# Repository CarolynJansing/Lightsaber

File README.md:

# Lightsaber
A lightsaber is a fictional energy sword featured in the Star Wars franchise. This project is a simulation of a lightsaber using LEDs, Sound and an Arduino microcontroller. It is based on the Gyversaber. https://www.instructables.com/Arduino-Based-Lightsaber-With-Light-and-Sound-Effe/

## Files

ArduinoCode : GyverSaber/GyverSaber/Gyversaber.ino

SD Files : GyverSaber/SDsounds

Schemes: PCB/

## Getting Started
These instructions will help you get a copy of the project up and running on your local machine for development and testing purposes.

### Prerequisites
To use this project, you will need the following:

Arduino IDE (https://www.arduino.cc/software)
•	Arduino NANO 
•	Adressable LED stripes WS2811, 12V
•	Button with LED 
•	MPU6050 
•	DF-Player
•	Batteries 18650 with Protection
•	DCDC Step-Down
•	Speaker
•	Resistors
•	Power button
•	Charging port
•	CC CV Charger for 3 cells
•	PCB-Board
•	Blade Pipe
•	PVC Pipes for hilt
•	Wire
•	3D druck
•	Soldering Supplies
I chose to use an PCB aswell you can configure it with my files on JLCPCB

### Installing
Clone the repository to your local machine: git clone https://github.com/CarolynJansing/Lightsaber.git
Open the Arduino IDE and open the Gyversaber.ino file from the cloned repository.
Connect the Arduino microcontroller to your computer using a USB cable.
Select the correct board and port in the Arduino IDE (Tools > Board and Tools > Port).
Upload the code to the Arduino microcontroller.
### Usage
The lightsaber can be controlled by the button. The buttons can be used to turn the lightsaber on and off, change the color of the lightsaber, and change the lightsaber mode.

## Built With
Arduino Nano following the Gyversaber Instructions and changed to a DFPlayer
## Author
Carolyn Jansing - CarolynJansing
+ MadGyver
License
This project is licensed under the MIT License - see the LICENSE file for details.

## Acknowledgments
The Star Wars franchise for inspiration and MadGyver.

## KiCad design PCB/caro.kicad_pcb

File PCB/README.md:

Project files fro KiCad.

Created and designed by @simonmicro with :hearts: 2022

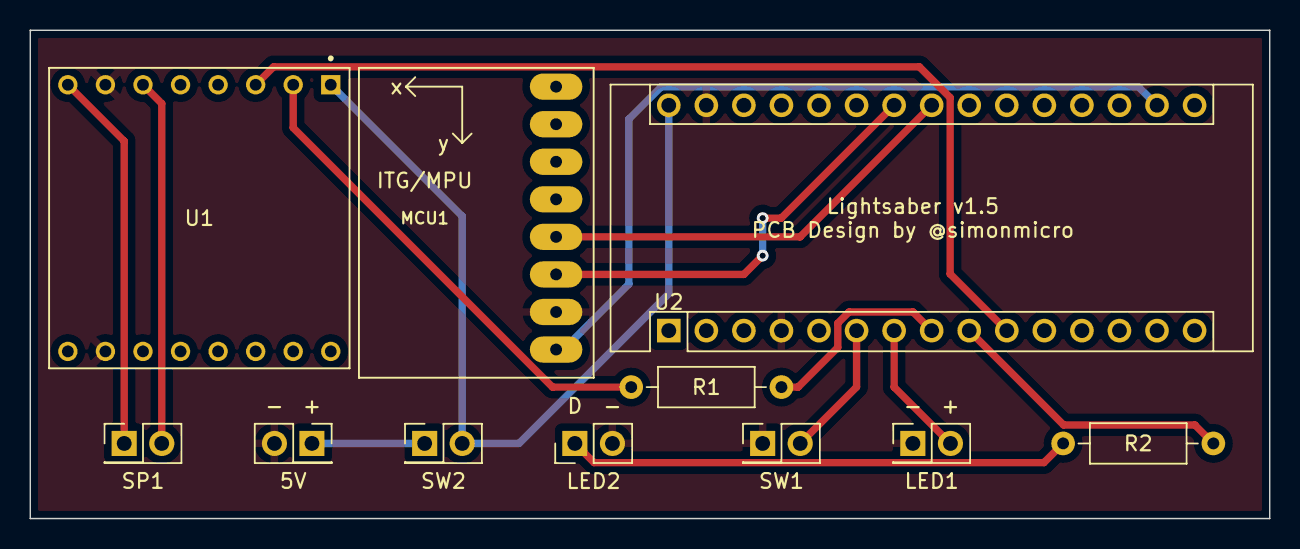
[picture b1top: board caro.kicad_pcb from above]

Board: 2 copper layers, 83.8 x 33.0 mm, 11 parts (0 on the bottom side), 15 nets.

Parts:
5V: PinSocket_2x01_P2.54mm_Vertical
LED1: Control Button LED; PinHeader_2x01_P2.54mm_Vertical
LED2: WS2811; PinHeader_1x02_P2.54mm_Vertical
MCU1: GY-521
R1, R2: 1000Ohm; R_Axial_DIN0207_L6.3mm_D2.5mm_P10.16mm_Horizontal
SP1: Speaker; PinHeader_2x01_P2.54mm_Vertical
SW1: Control Button; PinHeader_2x01_P2.54mm_Vertical
SW2: Power Switch; PinHeader_2x01_P2.54mm_Vertical
U1: DFR0299; MODULE_DFR0299
U2: Arduino_Nano_v3.x; Arduino_Nano

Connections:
3.3V: MCU1.1 (VCC), U2.17 (3V3)
5V: SW2.2 (B), U1.1 (VCC), U2.30 (VIN)
+5V: 5V.1, SW2.1 (A)
A4: MCU1.4 (SDA), U2.23 (A4)
A5: MCU1.3 (SCL), U2.24 (A5)
D3: SW1.1, U2.6 (D3)
D4: LED1.2 (A), U2.7 (D4)
D5: R1.1, U2.8 (D5)
D6: R2.1, U2.9 (D6)
D7: U1.3 (TX), U2.10 (D7)
GND: 5V.2, LED1.1 (K), LED2.2 (OUTG), MCU1.2 (GND), SW1.2, U1.7 (GND), U1.10 (GND), U2.4 (GND), U2.29 (GND)
unnamed: R1.2, U1.2 (RX)
unnamed: LED2.1 (OUTR), R2.2
unnamed: SP1.1, U1.8 (SPK2)
unnamed: SP1.2, U1.6 (SPK1)

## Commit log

2022-11-13 Changed to DFplayer
2022-11-13 Deleted other projects
2022-11-14 DF sound fix
2022-11-15 fix btn tick function
2022-11-16 Added KiCad files
2022-11-16 sound test + gradient
2022-11-26 Corrected inverted LED pins
2022-11-27 Bump to v1.1
2022-11-27 Updated annotations Added missing control LED Reduced resistor sizes
2022-11-27 Revision v1.3 Increased HIGH_PWR width to 2mm
2022-11-27 Revision v1.4 Swapped MCU and SDCard
2022-11-27 Moved resistor to increase distance to HIGH_PWR tracks
2022-11-27 Corrected worng annotation
2022-12-29 Changed some functions for testing MPU
2023-01-18 CleanUp code + rename Folder
2023-01-22 Revision udate to v1.5 Swapped WS2812b to WS2811
2023-04-11 Changes to fit for esp
2023-04-12 ports
2023-05-24 added wlan class,header and init in main
2023-05-24 save of last commit
2023-05-31 WLAN and MQTT draft
2023-06-07 fix mqtt
2023-06-14 fix wifi function test
2023-06-26 mqtt comment out
